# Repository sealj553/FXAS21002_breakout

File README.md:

# FXAS21002 breakout

This is a modified version of [William Laney's breakout](https://github.com/WLaney/FXAS21002-gyro-PCB) designed to be as small as possible.

Note: The SAO pin is pulled to GND, so the I2C address will be 0x20. If you are using a library that hardcodes the address to 0x21 (Adafruit's for instance), you may need to modify it.

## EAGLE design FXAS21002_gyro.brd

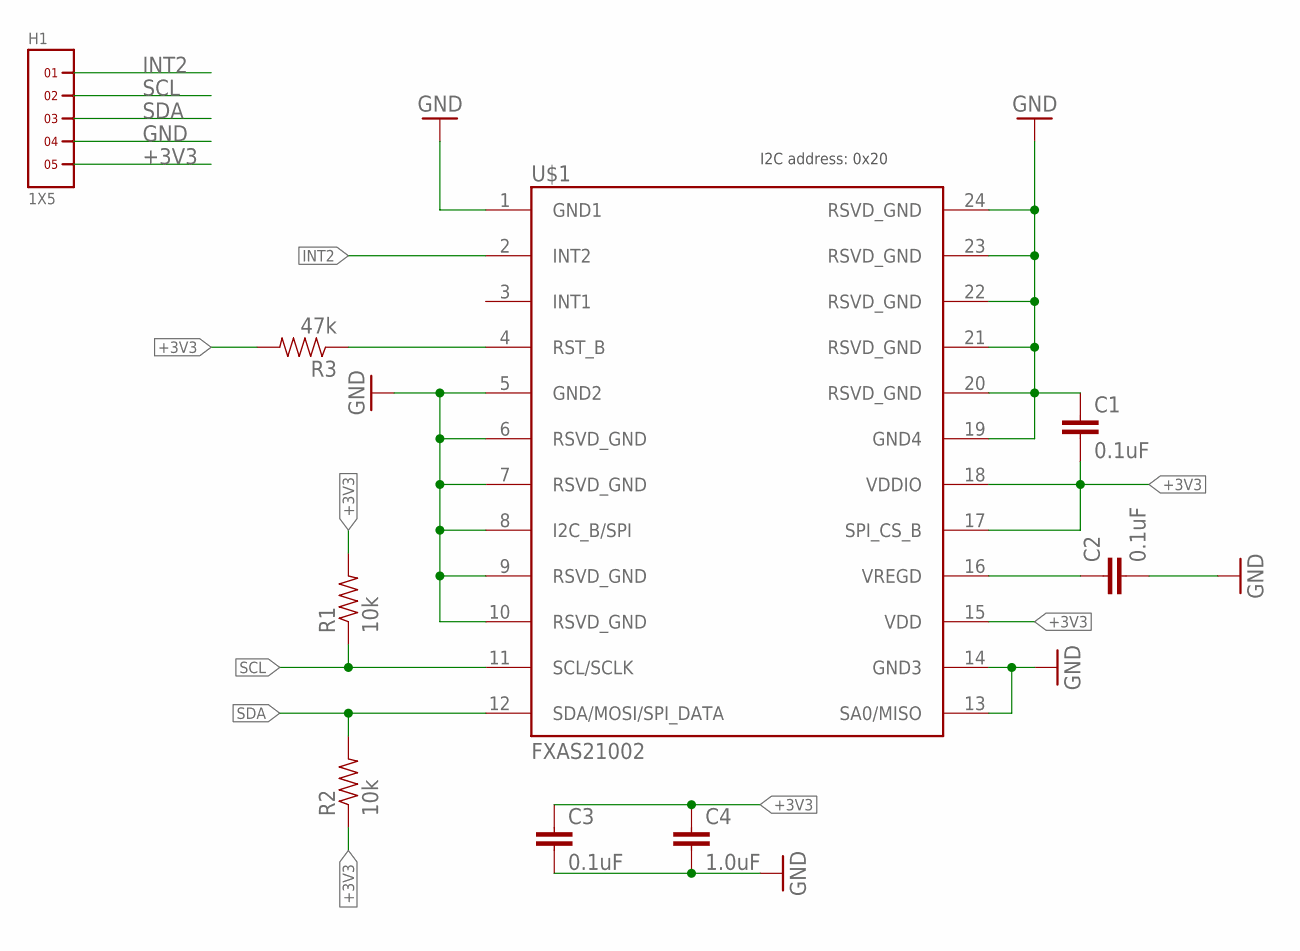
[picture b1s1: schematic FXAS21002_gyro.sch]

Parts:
C1, C2, C3: 0.1uF; 0805
C4: 1.0uF; 0805
H1: 1X5
R1, R2: 10k; 0805
R3: 47k; 0805
U$1: FXAS21002; 24QFN

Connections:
+3V3: C1.2, C3.1, C4.1, H1.5, R1.2, R2.1, R3.2, U$1.15 (VDD), U$1.17 (SPI_CS_B), U$1.18 (VDDIO)
GND: C1.1, C2.2, C3.2, C4.2, H1.4, U$1.1 (GND1), U$1.5 (GND2), U$1.6 (RSVD_GND), U$1.7 (RSVD_GND), U$1.8 (I2C_B/SPI), U$1.9 (RSVD_GND), U$1.10 (RSVD_GND), U$1.13 (SA0/MISO), U$1.14 (GND3), U$1.19 (GND4), U$1.20 (RSVD_GND), U$1.21 (RSVD_GND), U$1.22 (RSVD_GND), U$1.23 (RSVD_GND), U$1.24 (RSVD_GND)
INT2: H1.1, U$1.2 (INT2)
unnamed: C2.1, U$1.16 (VREGD)
unnamed: R3.1, U$1.4 (RST_B)
SCL: H1.2, R1.1, U$1.11 (SCL/SCLK)
SDA: H1.3, R2.2, U$1.12 (SDA/MOSI/SPI_DATA)

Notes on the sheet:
I2C address: 0x20

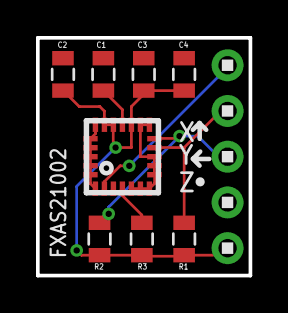
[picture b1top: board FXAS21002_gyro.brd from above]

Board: 2 copper layers, 11.8 x 13.2 mm, 9 parts (0 on the bottom side), 7 nets.

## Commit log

2019-04-18 fixed readme
2019-05-03 it works!

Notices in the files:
parts and their libraries:
SparkFun-Passives: Licensing: Creative Commons ShareAlike 4.0 International - https://creativecommons.org/licenses/by-sa/4.0
